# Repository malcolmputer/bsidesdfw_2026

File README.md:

# bsidesdfw_2026
BSidesDFW 2026 Electronic Badge

Designed By Malcolm Galland (malcolm@digitaldemolitions.com)

Art by Olivia Fisher (@livtostich)

Designed in KiCAD 10.0

Designed for order and assembly through JLCPCB

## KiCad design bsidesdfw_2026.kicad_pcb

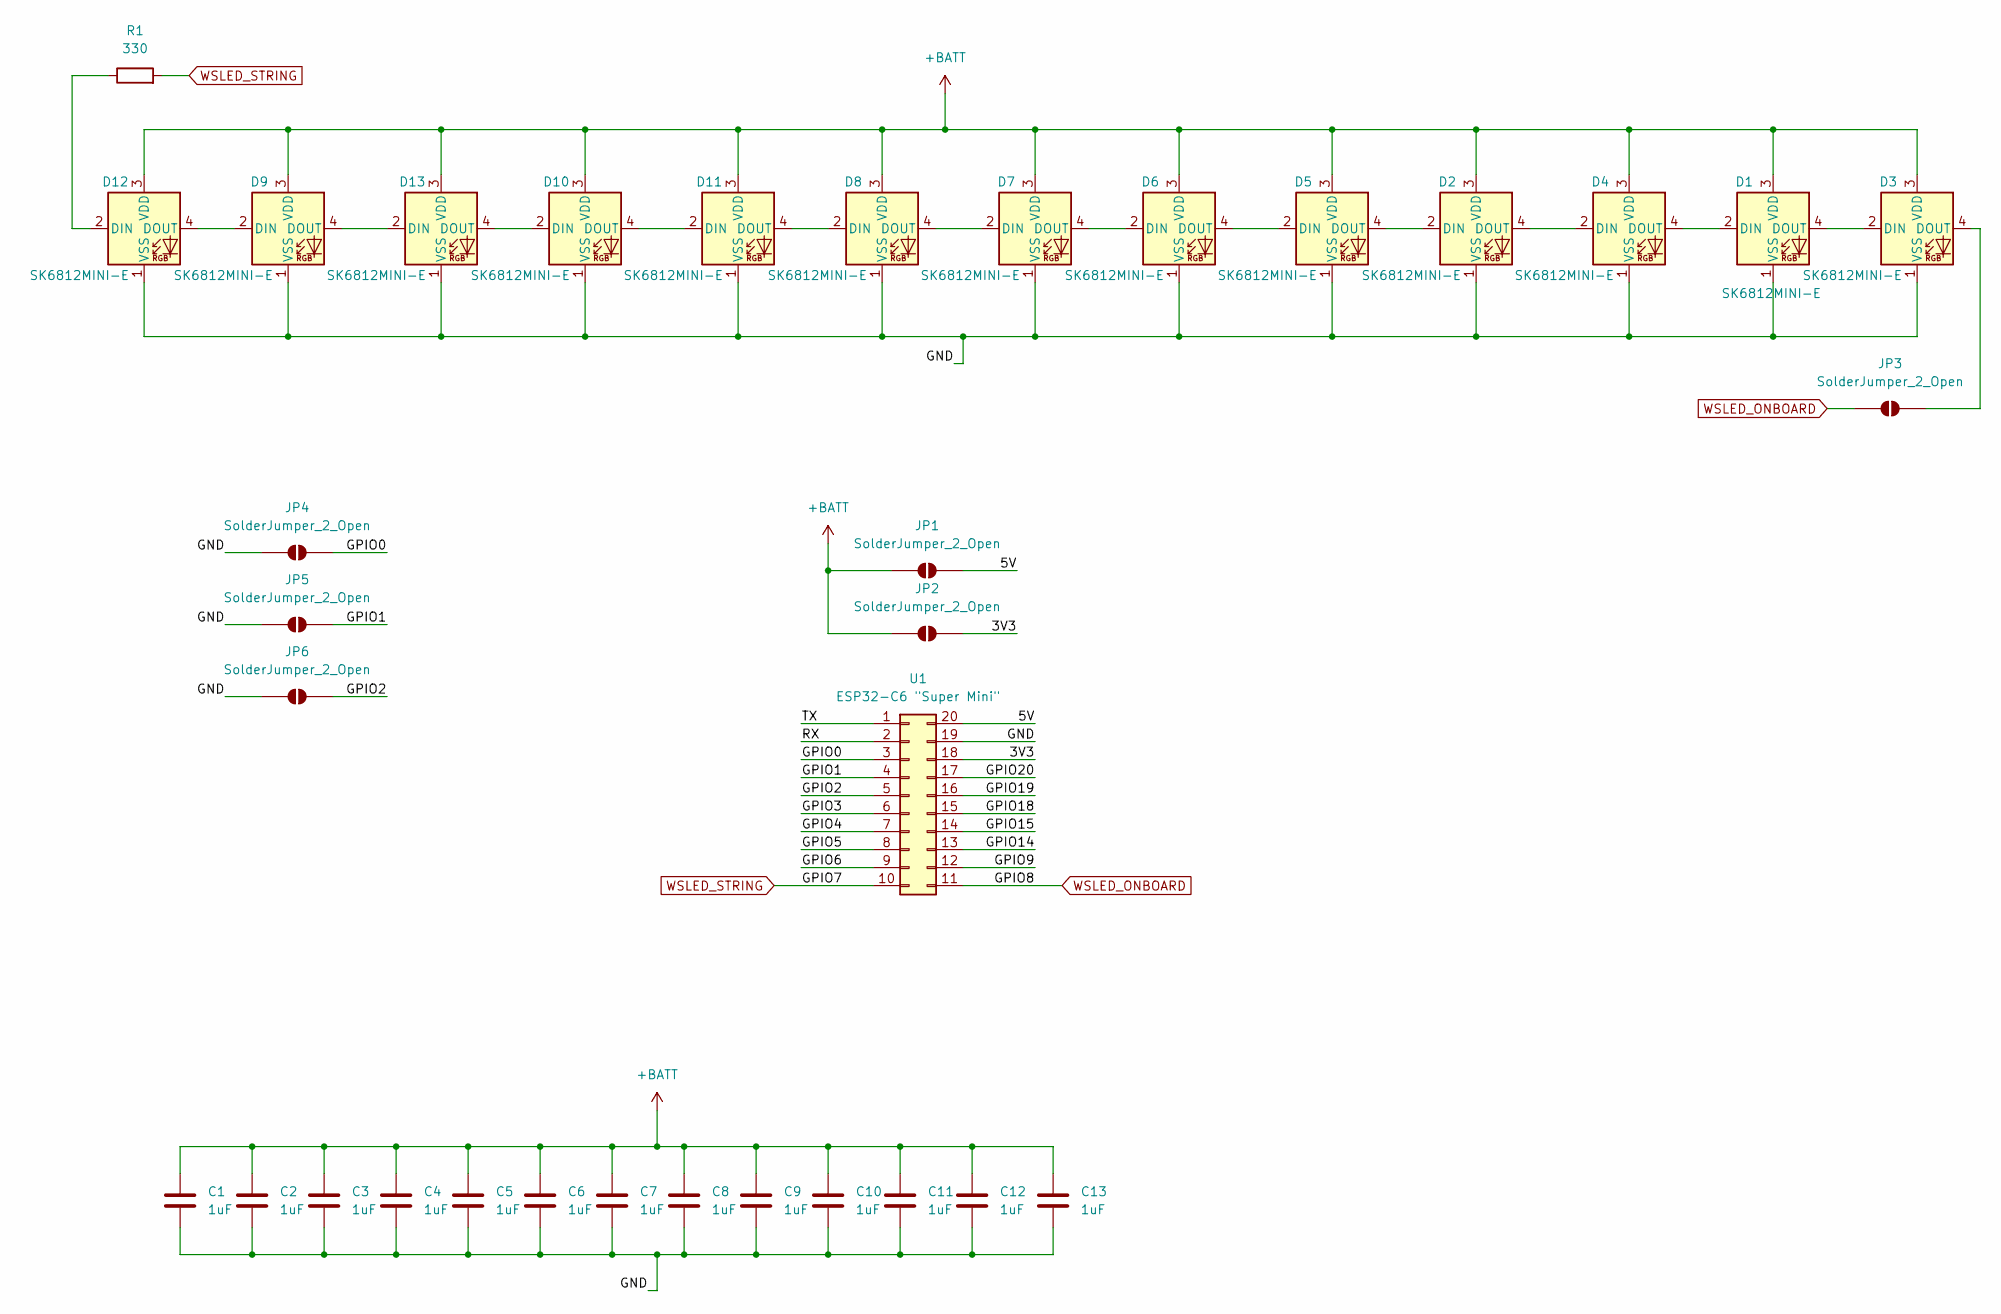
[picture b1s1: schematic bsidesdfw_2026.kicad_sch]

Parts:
C1, C2, C3, C4, C5, C6, C7, C8, C9, C10, C11, C12, C13: 1uF; Part Number CL05A105KA5NQNC; LCSC Part C52923
D1, D2, D3, D4, D5, D6, D7, D8, D9, D10, D11, D12, D13: SK6812MINI-E; LED_SK6812MINI-E_3.2x2.8mm_P1.5mm_ReverseMount; LCSC Part C5149201
JP1, JP2, JP3, JP4, JP5, JP6: SolderJumper_2_Open; SolderJumper-2_P1.3mm_Open_RoundedPad1.0x1.5mm
R1: 330; LCSC Part C25104
U1: ESP32-C6 "Super Mini"; ESP32-C6_Super_Mini

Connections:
+BATT: C1.1, C2.1, C3.1, C4.1, C5.1, C6.1, C7.1, C8.1, C9.1, C10.1, C11.1, C12.1, C13.1, D1.3 (VDD), D2.3 (VDD), D3.3 (VDD), D4.3 (VDD), D5.3 (VDD), D6.3 (VDD), D7.3 (VDD), D8.3 (VDD), D9.3 (VDD), D10.3 (VDD), D11.3 (VDD), D12.3 (VDD), D13.3 (VDD), JP1.1 (A), JP2.1 (A)
/3V3: JP2.2 (B), U1.18
/5V: JP1.2 (B), U1.20
/GND: C1.2, C2.2, C3.2, C4.2, C5.2, C6.2, C7.2, C8.2, C9.2, C10.2, C11.2, C12.2, C13.2, D1.1 (VSS), D2.1 (VSS), D3.1 (VSS), D4.1 (VSS), D5.1 (VSS), D6.1 (VSS), D7.1 (VSS), D8.1 (VSS), D9.1 (VSS), D10.1 (VSS), D11.1 (VSS), D12.1 (VSS), D13.1 (VSS), JP4.1 (A), JP5.1 (A), JP6.1 (A), U1.19
/GPIO0: JP4.2 (B), U1.3
/GPIO1: JP5.2 (B), U1.4
/GPIO2: JP6.2 (B), U1.5
/GPIO3: U1.6
/GPIO4: U1.7
/GPIO5: U1.8
/GPIO6: U1.9
/GPIO9: U1.12
/GPIO14: U1.13
/GPIO15: U1.14
/GPIO18: U1.15
/GPIO19: U1.16
/GPIO20: U1.17
/RX: U1.2
/TX: U1.1
unnamed: D1.2 (DIN), D4.4 (DOUT)
unnamed: D1.4 (DOUT), D3.2 (DIN)
unnamed: D2.2 (DIN), D5.4 (DOUT)
unnamed: D2.4 (DOUT), D4.2 (DIN)
unnamed: D3.4 (DOUT), JP3.2 (B)
unnamed: D5.2 (DIN), D6.4 (DOUT)
unnamed: D6.2 (DIN), D7.4 (DOUT)
unnamed: D7.2 (DIN), D8.4 (DOUT)
unnamed: D10.2 (DIN), D13.4 (DOUT)
unnamed: D10.4 (DOUT), D11.2 (DIN)
unnamed: D8.2 (DIN), D11.4 (DOUT)
unnamed: D12.2 (DIN), R1.1
unnamed: D9.2 (DIN), D12.4 (DOUT)
unnamed: D9.4 (DOUT), D13.2 (DIN)
WSLED_ONBOARD: JP3.1 (A), U1.11
WSLED_STRING: R1.2, U1.10

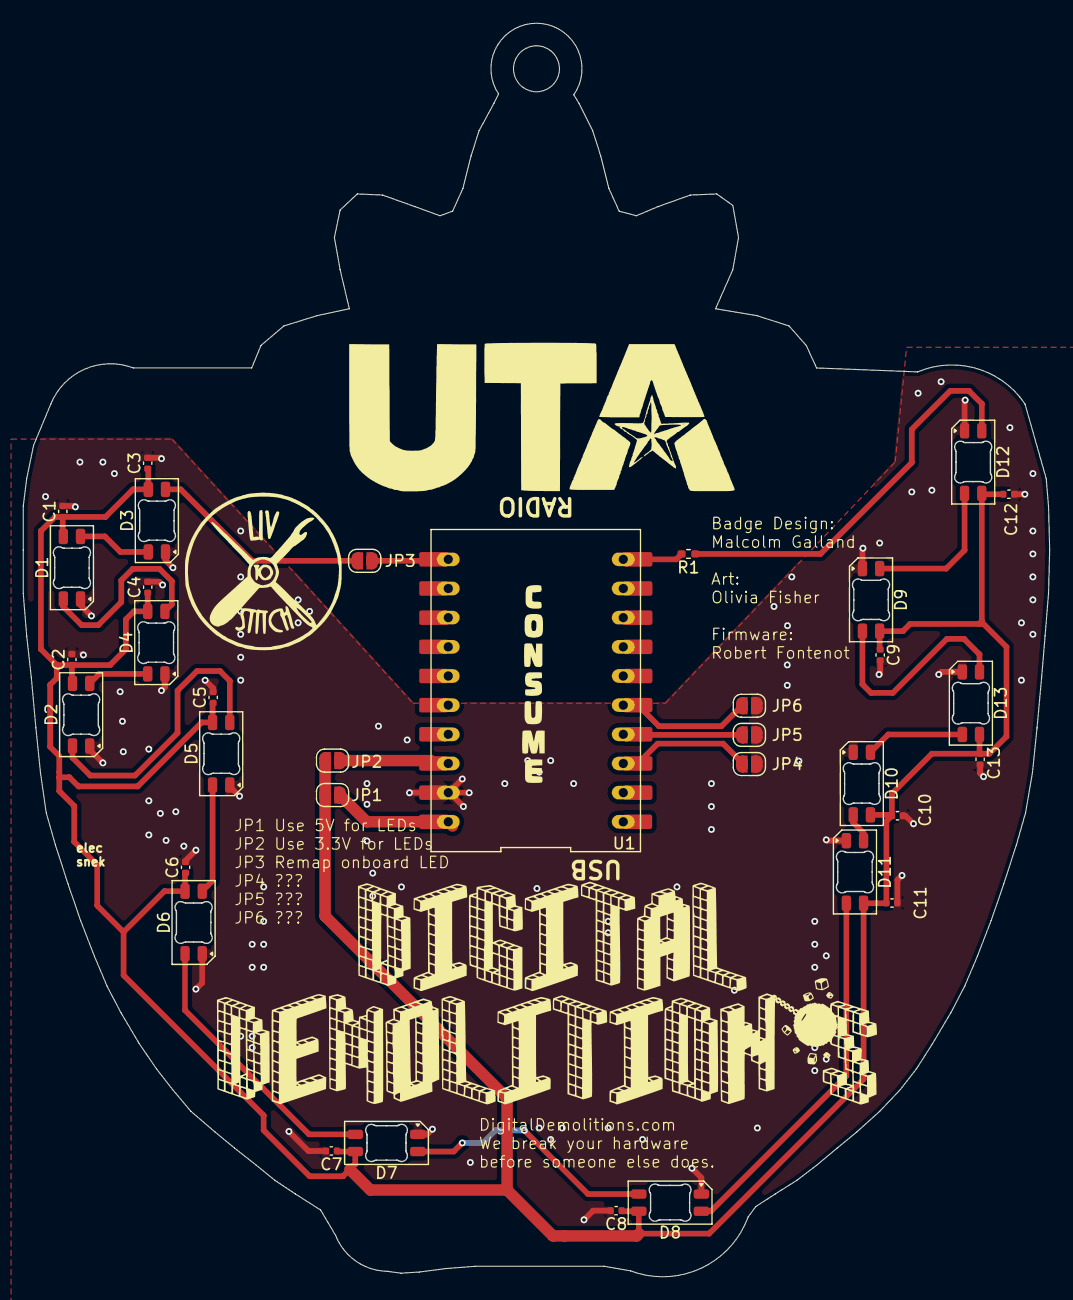
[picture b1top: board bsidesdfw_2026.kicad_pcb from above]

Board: 2 copper layers, 89.4 x 109.2 mm, 34 parts (0 on the bottom side), 23 nets.
